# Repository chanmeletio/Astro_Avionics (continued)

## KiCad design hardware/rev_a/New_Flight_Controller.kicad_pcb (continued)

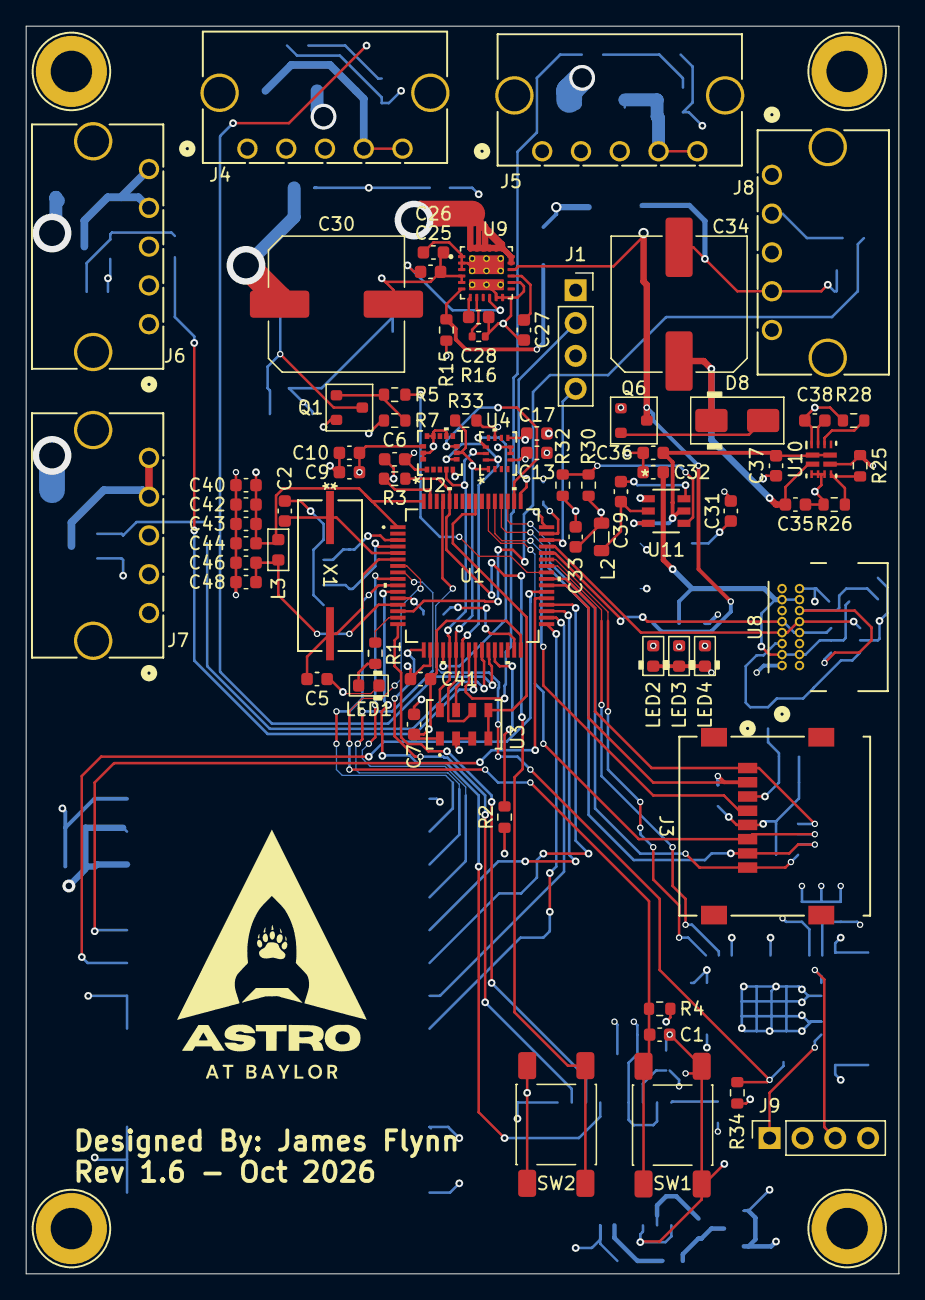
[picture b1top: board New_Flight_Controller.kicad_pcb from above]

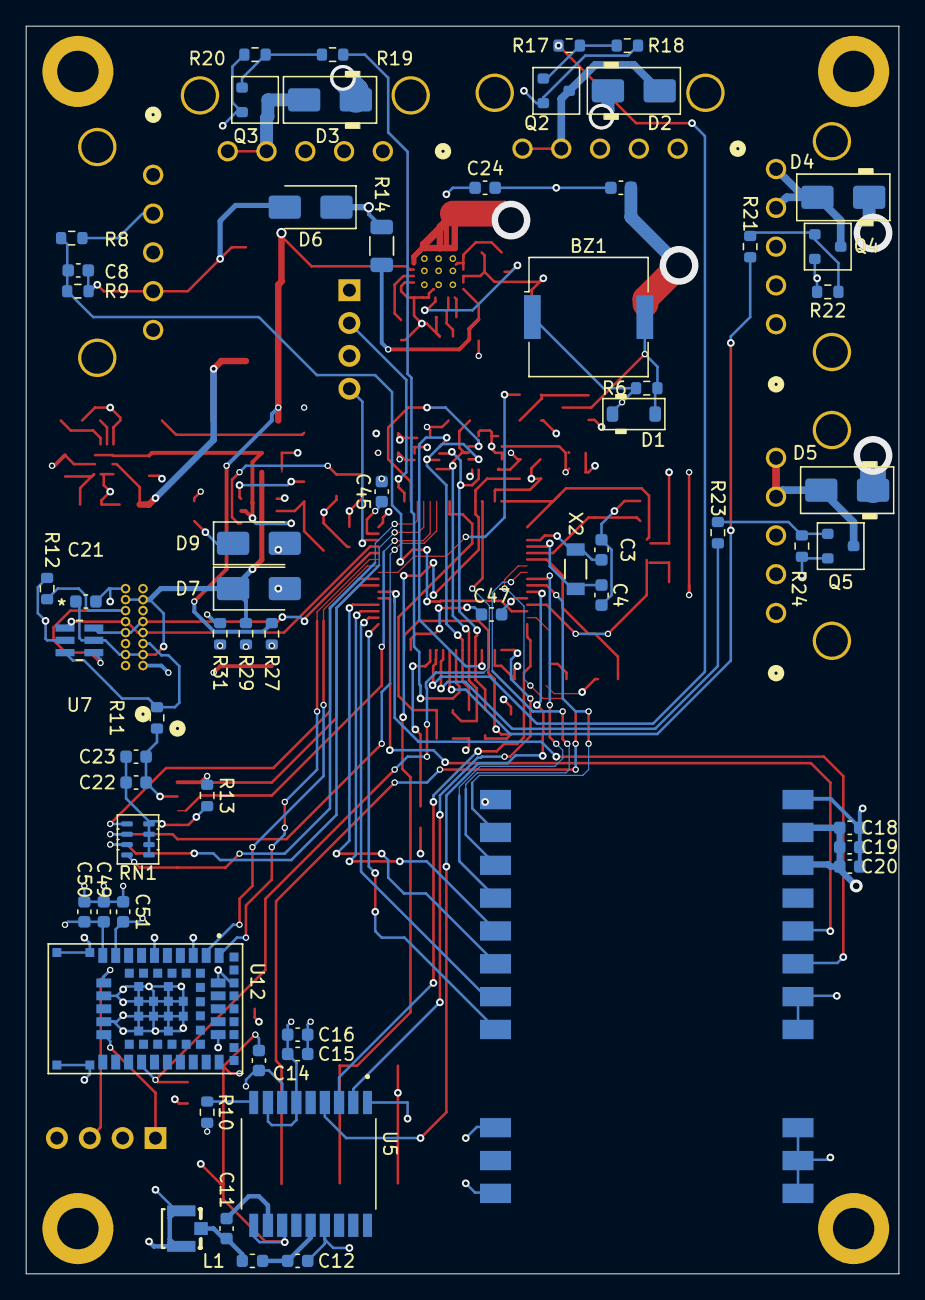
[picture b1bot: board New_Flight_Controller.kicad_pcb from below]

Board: 4 copper layers, 67.5 x 96.5 mm, 134 parts (61 on the bottom side), 89 nets.

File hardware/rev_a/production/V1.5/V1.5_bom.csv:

Designator,Footprint,Quantity,Value,LCSC Part #
BZ1,Buzzer_Murata_PKMCS0909E,1,Buzzer,C910763
"C1, C12, C13, C14, C16, C17, C18, C21, C23, C24, C29, C39, C40, C41, C42, C43, C44, C6, C7, C8, C9",0603,21,100nF,C1591
"C10, C19, C20, C26, C32, C35, C36, C37",0603,8,10uF,C96446
C11,0603,1,100pF,C14858
"C15, C22",0603,2,4.7uF,C19666
"C2, C5",0603,2,6.8pF,C318672
"C25, C27, C28, C38, C46",0603,5,10nF,C1589
"C3, C4",0603,2,12pF,C38523
"C30, C34",C_Elec_10x10.2,2,470uF_35V_-55C,C3350
"C31, C33",0603,2,22uF,C86295
"C45, C47",0603,2,2.2uF,C100082
C48,0603,1,1uF,C5199872
D1,D_SOD-123,1,1N4148W,C81598
"D2, D3, D4, D5, D8",D_SMA,5,B240A,C39358
D6,D_SMA,1,SMAJ9.0A,C113955
D7,D_SMA,1,SMAJ3.3A,C78401
D9,D_SMA,1,SMAJ3.3A,C2917853
J1,PinSocket_1x04_P2.54mm_Vertical,1,PINHD_1x4_Female,C41431927
J2,U.FL,1,U.FL,C5137195
J3,CONN_47219-2001_MOL,1,472192001,C164170
"J4, J5, J6, J7, J8",CONN_SD-43650-002_05_MOL,5,436500503,C19793673
L1,0603,1,27nH @2GHz,C162550
L2,0805,1,10uH,C76742
L3,Ferrite_0603_1608Metric,1,1k Ohm @ 100mHz,C883597
LED1,0603,1,LED_0603_Blue,C2288
LED2,0603,1,LED_0603_Red,C2286
LED3,0603,1,LED_0603_Amber,C2287
LED4,0603,1,LED_0603_Green,C12624
Q1,SOT-23,1,IRLML2502,C21713837
"Q2, Q3, Q4, Q5",SOT-23,4,IRLML6344,C6285738
Q6,SOT-23,1,DMP3099L,C2940610
"R1, R31, R6",0603,3,1k,C14676
"R10, R13, R18, R2, R20, R22, R24, R3, R32, R33, R4, R7",0603,12,10k,C99198
"R11, R12",0603,2,5.1k,C105580
R14,1206,1,370k,C3018094
"R15, R8",0603,2,100k,C14675
R16,0402,1,12.5k,C6666801
"R17, R19, R21, R23, R5",0603,5,100,C105588
R25,0603,1,82k,C137678
"R26, R28",0603,2,24k,C23352 
R27,0603,1,4.7k,C99782
R29,0603,1,2.2k,C114662
R30,0603,1,45.3k,C227910
R9,0603,1,47k,C111134
RN1,R_Array_Concave_4x0603,1,R_10k_4x1206,C110924
"SW1, SW2",SW_Push_1P1T_NO_E-Switch_TL3301NxxxxxG,2,~,C592734
U1,LQFP64-10x10mm,1,STM32F405RGT7TR,C2054405
U10,RUX0012A,1,TPS2121RUXR,C485916
U11,SOT23_DDC_TEX,1,LMR51420XDDCR,C5246146
U2,QFN_31DLTR_STM,1,H3LIS331DLTR,C2655074
U3,SON8_MS5611_TEC,1,MS560702BA03-50,C97627
U4,BMI270_BOS,1,BMI270,C2836813
U5,XCVR_MAX-M10S-00B,1,MAX-M10S-00B,C4153167
U6,E22-400M30S,1,E22-400M30S,C411292
U7,DBV6,1,TPD4E001DBVR,C465736
U8,2137160001_MOL,1,2137160001,C5119949
U9,IC_TPS259830LNRGER,1,TPS259830ONRGER,C20611808
X1,ABLS-8.000MHZ-B2-T_ABR,1,ABLS-8.000MHZ-B2-T,C596837
X2,CAP_ABS07-32.768KHZ-T_ABR,1,ABS07-32.768KHZ-T,C130253

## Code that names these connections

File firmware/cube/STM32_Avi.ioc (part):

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Mcu.Name=STM32F405RGTx
Mcu.Package=LQFP64
Mcu.UserName=STM32F405RGTx
PA0-WKUP.Signal=ADCx_IN0
PA1.Signal=GPIO_Output
PA10.Signal=USART1_RX
PA11.Mode=Device_Only
PA11.Signal=USB_OTG_FS_DM
PA12.Mode=Device_Only
PA12.Signal=USB_OTG_FS_DP
PA13.Mode=Serial_Wire
PA13.Signal=SYS_JTMS-SWDIO
PA14.Mode=Serial_Wire
PA14.Signal=SYS_JTCK-SWCLK
PA15.Signal=GPIO_Output
PA2.Mode=Asynchronous
PA2.Signal=USART2_TX
PA3.Mode=Asynchronous
PA3.Signal=USART2_RX
PA4.Signal=GPIO_Output
PA5.Mode=Full_Duplex_Master
PA5.Signal=SPI1_SCK
PA6.Mode=Full_Duplex_Master
PA6.Signal=SPI1_MISO
PA7.Mode=Full_Duplex_Master
PA7.Signal=SPI1_MOSI
PA8.Signal=S_TIM1_CH1
PA9.Signal=USART1_TX
PB0.Signal=GPIO_Output
PB1.Signal=GPIO_Output
PB12.Signal=GPIO_Output
PB13.Mode=Full_Duplex_Master
PB13.Signal=SPI2_SCK
PB14.Mode=Full_Duplex_Master
PB14.Signal=SPI2_MISO
PB15.Mode=Full_Duplex_Master
PB15.Signal=SPI2_MOSI
PB2.Signal=GPIO_Input
PB4.Signal=GPIO_Output
PB8.Signal=GPIO_Output
PC0.Signal=GPIO_Input
PC1.Signal=GPIO_Output
PC10.Mode=SD_4_bits_Wide_bus
PC10.Signal=SDIO_D2
PC11.Mode=SD_4_bits_Wide_bus
PC11.Signal=SDIO_D3
PC12.Mode=SD_4_bits_Wide_bus
PC12.Signal=SDIO_CK
PC14-OSC32_IN.Mode=LSE-External-Oscillator
PC14-OSC32_IN.Signal=RCC_OSC32_IN
PC15-OSC32_OUT.Mode=LSE-External-Oscillator
PC15-OSC32_OUT.Signal=RCC_OSC32_OUT
PC2.Signal=GPXTI2
PC3.Signal=GPXTI3
PC4.Signal=GPIO_Output
PC5.Signal=GPIO_Output
PC6.Signal=GPIO_Output
PC7.Signal=GPIO_Output
PC8.Mode=SD_4_bits_Wide_bus
PC8.Signal=SDIO_D0
PC9.Mode=SD_4_bits_Wide_bus
PC9.Signal=SDIO_D1
PD2.Mode=SD_4_bits_Wide_bus
PD2.Signal=SDIO_CMD
PH0-OSC_IN.Mode=HSE-External-Oscillator
PH0-OSC_IN.Signal=RCC_OSC_IN
PH1-OSC_OUT.Mode=HSE-External-Oscillator
PH1-OSC_OUT.Signal=RCC_OSC_OUT
RCC.HSE_VALUE=8000000
RCC.SYSCLKFreq_VALUE=168000000
RCC.SYSCLKSource=RCC_SYSCLKSOURCE_PLLCLK
board=custom
